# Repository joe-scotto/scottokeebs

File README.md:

ScottoKeebs at its core is an extensive collection of freely available handwired keyboard and macropad projects. It was started in September of 2022 and since then over 19 projects have been released. Most of them fit on a common 220x220mm 3D printer, require minimal support material, and use either an Arduino Pro Micro or a more powerful Raspberry Pi Pico.

# Navigation

-   [Website](https://scottokeebs.com)
-   [Keyboards](https://scottokeebs.com/blogs/keyboards)
-   [Macropads](https://scottokeebs.com/blogs/macropads)
-   [Extras](https://github.com/joe-scotto/scottokeebs/tree/main/Extras)
-   [Discord](https://discord.gg/vN6X3z8eyv)
-   [YouTube](https://youtube.com/joe_scotto)
-   [Recommendations](https://scottokeebs.com/pages/recommendations)
-   [Handwiring](https://www.youtube.com/watch?v=hjml-K-pV4E)
-   [Shop](https://www.youtube.com/watch?v=hjml-K-pV4E)

# Supporting

The ScottoKeebs project is released entirely for free and always will be, however, the development of new boards is completely out of my own pocket. It’s not a particularly expensive project to maintain but does involve quite a bit of time between prototyping and making content related to them.

**If you happen to really enjoy what I do and want to support me, consider [donating](https://donate.stripe.com/eVa14Yev83SmavmbII), [becoming a patron](https://patreon.com/joe_scotto), or purchasing something from my [shop](https://www.scottokeebs.com/shop).**

# License

</a></p>

<p xmlns:cc="http://creativecommons.org/ns#" xmlns:dct="http://purl.org/dc/terms/"><a property="dct:title" rel="cc:attributionURL" href="https://github.com/joe-scotto/scottokeebs">ScottoKeebs</a> by <a rel="cc:attributionURL dct:creator" property="cc:attributionName" href="https://github.com/joe-scotto">Joe Scotto</a> is licensed under <a href="http://creativecommons.org/licenses/by-nc-sa/4.0/?ref=chooser-v1" target="_blank" rel="license noopener noreferrer" style="display:inline-block;">CC BY-NC-SA 4.0

_If you plan on converting a ScottoKeeb to a PCB, I would prefer you don't release the production or design files publicly in order to prevent people from stealing and selling my designs._

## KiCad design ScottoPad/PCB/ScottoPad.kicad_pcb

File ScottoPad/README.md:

# ScottoPad (SK33)

The ScottoPad is an 18-key wireless macropad.

You can read more about the components and how to build it [here](https://scottokeebs.com/blogs/macropads/scottopad-handwired-macropad).

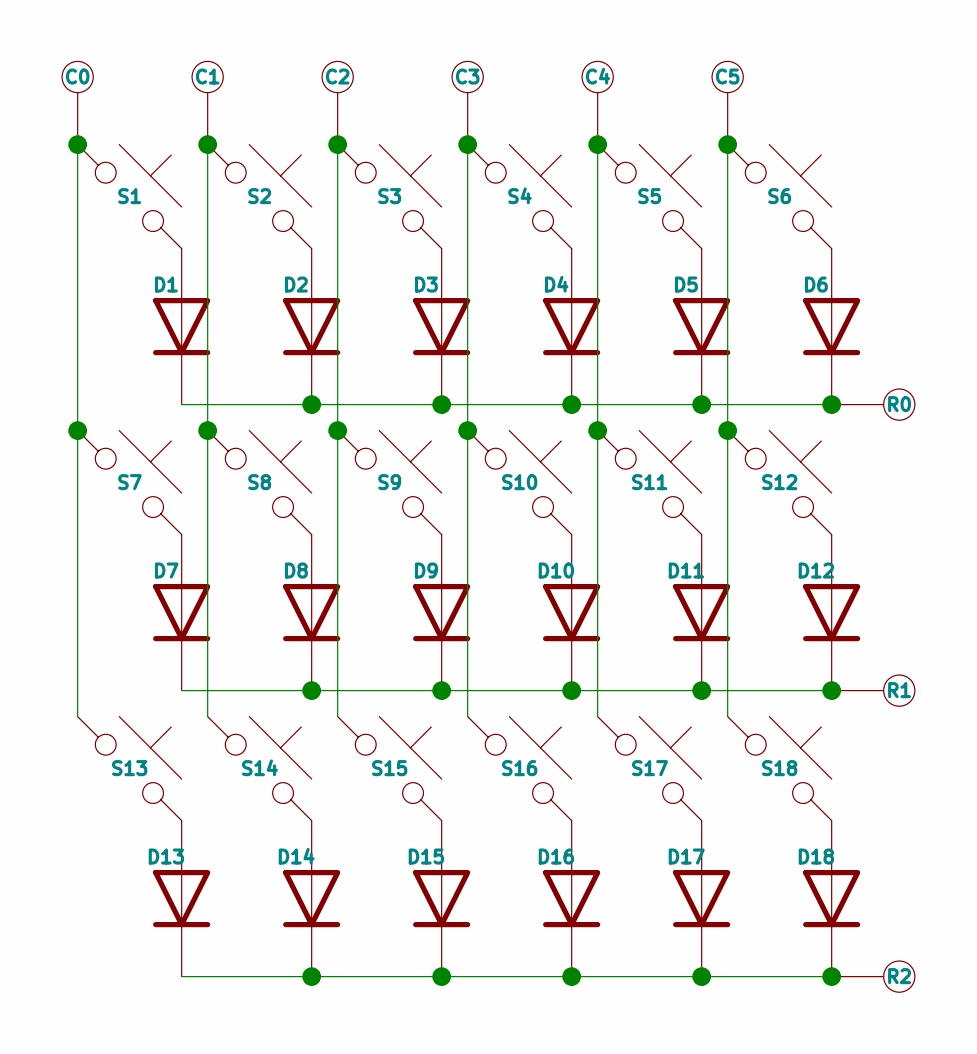
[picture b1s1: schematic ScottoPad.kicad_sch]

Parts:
C0, C1, C2, C3, C4, C5: TestPoint
D1, D2, D3, D4, D5, D6, D7, D8, D9, D10, D11, D12, D13, D14, D15, D16, D17, D18: Diode; Diode_SOD-123
R0, R1, R2: TestPoint
S1, S2, S3, S4, S5, S6, S7, S8, S9, S10, S11, S12, S13, S14, S15, S16, S17, S18: Keyswitch; MX_Solder_1.00u

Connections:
unnamed: C0.1, S1.1, S7.1, S13.1
unnamed: C1.1, S2.1, S8.1, S14.1
unnamed: C2.1, S3.1, S9.1, S15.1
unnamed: C3.1, S4.1, S10.1, S16.1
unnamed: C4.1, S5.1, S11.1, S17.1
unnamed: C5.1, S6.1, S12.1, S18.1
unnamed: D1.2 (A), S1.2
unnamed: D1.1 (K), D2.1 (K), D3.1 (K), D4.1 (K), D5.1 (K), D6.1 (K), R0.1
unnamed: D2.2 (A), S2.2
unnamed: D3.2 (A), S3.2
unnamed: D4.2 (A), S4.2
unnamed: D5.2 (A), S5.2
unnamed: D6.2 (A), S6.2
unnamed: D7.2 (A), S7.2
unnamed: D8.2 (A), S8.2
unnamed: D9.2 (A), S9.2
unnamed: D10.2 (A), S10.2
unnamed: D7.1 (K), D8.1 (K), D9.1 (K), D10.1 (K), D11.1 (K), D12.1 (K), R1.1
unnamed: D11.2 (A), S11.2
unnamed: D12.2 (A), S12.2
unnamed: D13.2 (A), S13.2
unnamed: D13.1 (K), D14.1 (K), D15.1 (K), D16.1 (K), D17.1 (K), D18.1 (K), R2.1
unnamed: D14.2 (A), S14.2
unnamed: D15.2 (A), S15.2
unnamed: D16.2 (A), S16.2
unnamed: D17.2 (A), S17.2
unnamed: D18.2 (A), S18.2

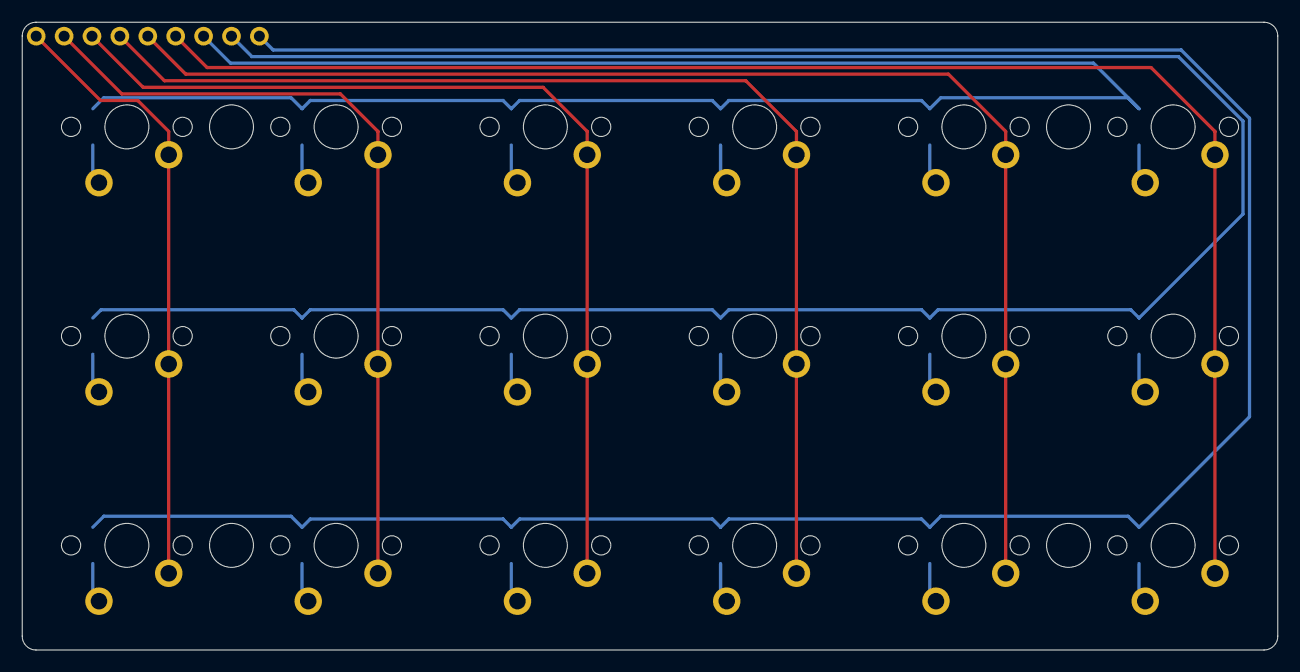
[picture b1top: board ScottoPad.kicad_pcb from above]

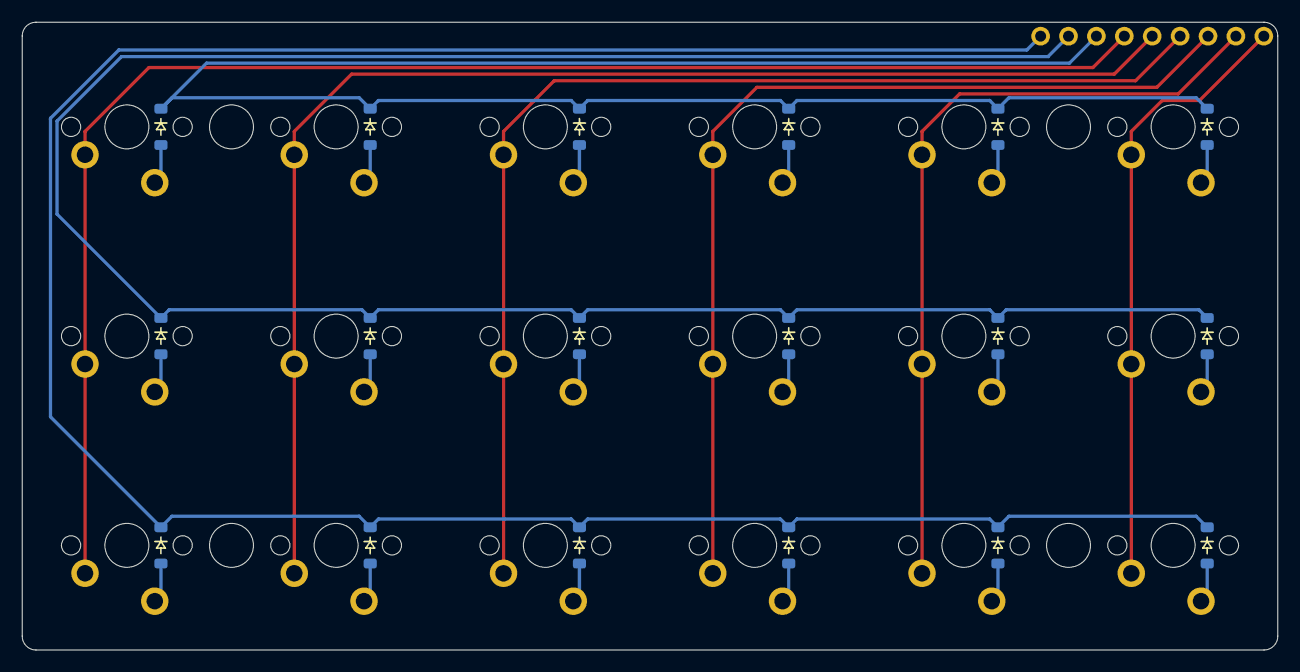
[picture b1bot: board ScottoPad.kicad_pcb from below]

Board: 2 copper layers, 114.3 x 57.2 mm, 45 parts (18 on the bottom side), 27 nets.

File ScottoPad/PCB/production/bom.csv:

Designator,Footprint,Quantity,Value,LCSC Part #
"C0, C1, C2, C3, C4, C5, R0, R1, R2",TestPoint,9,TestPoint,
"D1, D10, D11, D12, D13, D14, D15, D16, D17, D18, D2, D3, D4, D5, D6, D7, D8, D9",Diode_SOD-123,18,Diode,
"S1, S10, S11, S12, S13, S14, S15, S16, S17, S18, S2, S3, S4, S5, S6, S7, S8, S9",MX_Solder_1.00u,18,Keyswitch,

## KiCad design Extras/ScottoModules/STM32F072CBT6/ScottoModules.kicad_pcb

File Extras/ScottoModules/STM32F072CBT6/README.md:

# ScottoModules

Two modules based on the STM32F072CBT6 to make integrated MCU PCBs simpler. They're designed to sit between 2 switches on an ortholinear or row-staggered keyboard, column-staggered will require some manual moving to get them to fit correctly.

# Bill of Materials (BOM)

| Quantity | Part                        | LCSC                                                                               |
| -------- | --------------------------- | ---------------------------------------------------------------------------------- |
| 1        | STM32F072CBT6 (LQFP-48_7x7) | [C81720](https://jlcpcb.com/partdetail/Stmicroelectronics-STM32F072CBT6/C81720)    |
| 1        | XC6206 (SOT-23-3L)          | [C5446](https://jlcpcb.com/partdetail/TorexSemicon-XC6206P332MRG/C5446)            |
| 1        | USBLC6-2SC6 (SOT-23-6)      | [C2827654](https://jlcpcb.com/partdetail/TechPublic-USBLC62SC6/C2827654)           |
| 1        | TL3342                      | [C115351](https://jlcpcb.com/partdetail/Alpsalpine-SKQGABE010/C115351)             |
| 1        | USB_C_HRO_TYPE-C-31-M-12    | [C165948](https://jlcpcb.com/partdetail/Korean_HropartsElec-TYPE_C_31_M12/C165948) |
| 2        | 5.1k Resistor (0402)        | [C25905](https://jlcpcb.com/partdetail/26648-0402WGF5101TCE/C25905)                |
| 1        | 10k Resistor (0402)         | [C25744](https://jlcpcb.com/partdetail/26487-0402WGF1002TCE/C25744)                |
| 1        | 500mA Fuse (0603)           | [C210357](https://jlcpcb.com/partdetail/Bourns-MF_FSMF050X2/C210357)               |
| 3        | 1uF Capacitor (0402)        | [C52923](https://jlcpcb.com/partdetail/53938-CL05A105KA5NQNC/C52923)               |
| 1        | 10nF Capacitor (0402)       | [C15195](https://jlcpcb.com/partdetail/15869-CL05B103KB5NNNC/C15195)               |
| 2        | 4.7uF Capacitor (0402)      | [C23733](https://jlcpcb.com/partdetail/24469-CL05A475MP5NRNC/C23733)               |
| 5        | 100nF Capacitor (0402)      | [C307331](https://jlcpcb.com/partdetail/291005-CL05B104KB54PNC/C307331)            |

# Usage

1. The project is setup as a Kicad template, first open Kicad and select "New Project from Template..." from the file menu.

2. Next click the folder icon and navigate to where you saved the `ScottoModules/STM32F072CBT6` folder and open it.

3. Select `ScottoModules (STM32)` and click `OK`.

4. Name your project and save it somewhere.

5. You're now ready to start using ScottoModules!

# Kicad Template Folder

Alternatively, you can save `ScottoModules/STM32F072CBT6` to your Kicad templates folder and not have to manually load it each time.

-   **Mac** - /Users/YOUR_USERNAME/Documents/KiCad/8.0/template/
-   **Windows** - C:\Users\YOUR_USERNAME\Documents\KiCad\8.0\template\

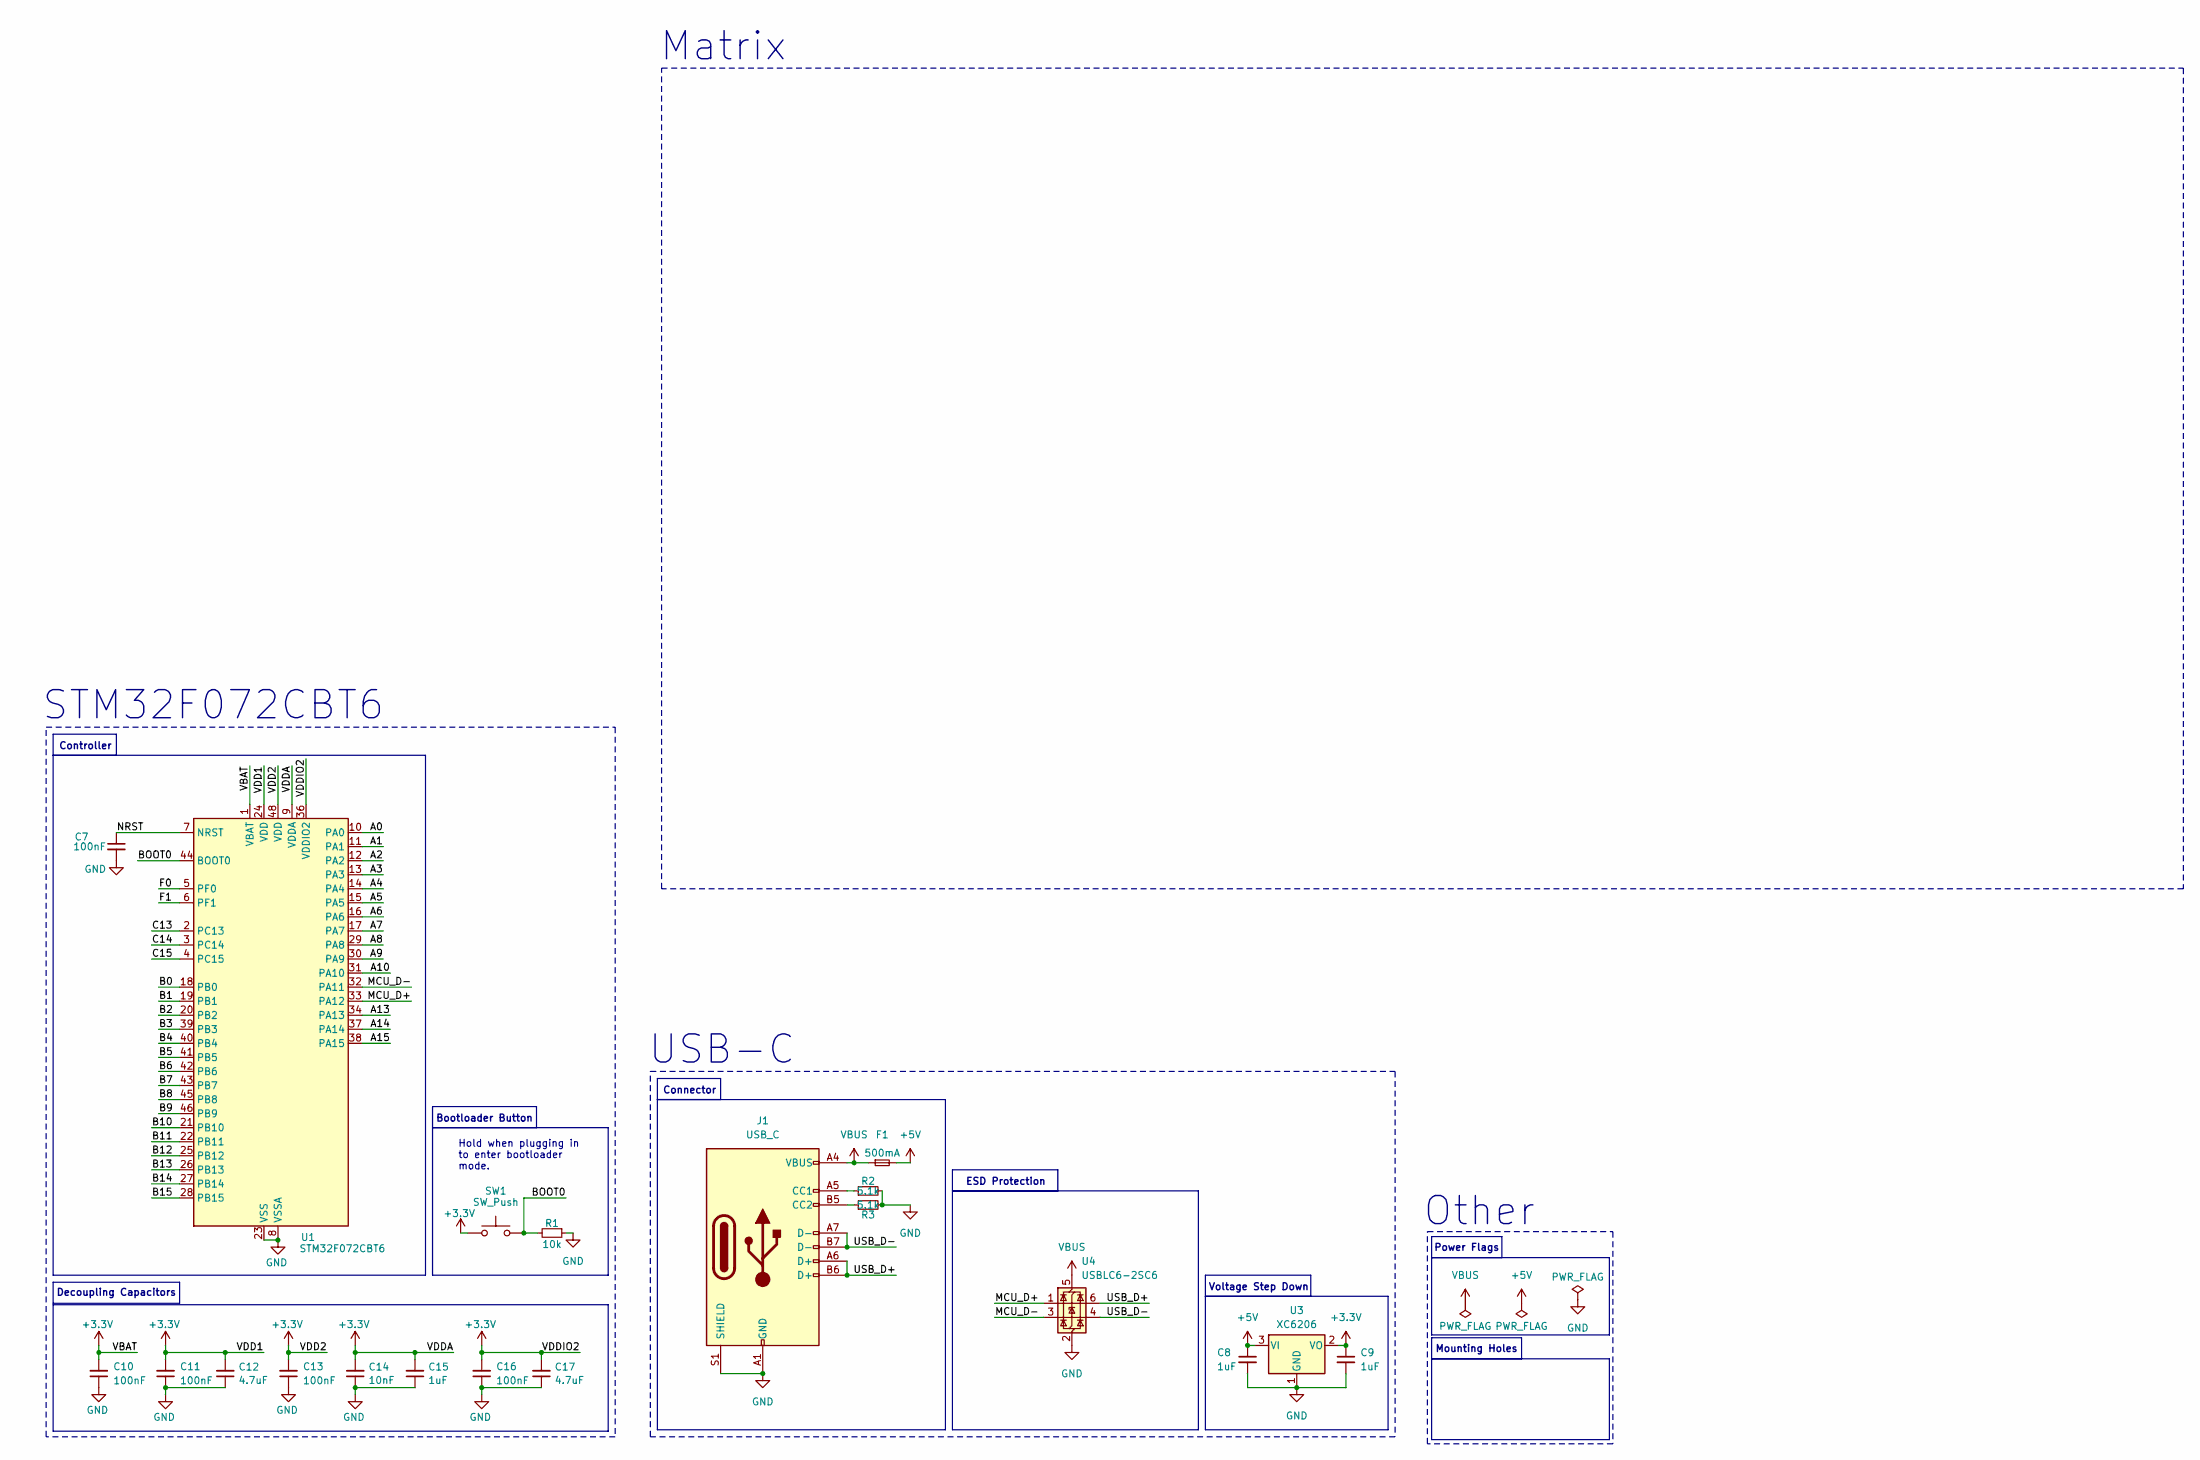
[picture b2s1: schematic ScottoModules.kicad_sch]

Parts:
C7: 100nF; Capacitor_0402; LCSC C307331
C8, C9: 1uF; Capacitor_0402; LCSC C52923
C10, C11, C13, C16: 100nF; Capacitor_0402; MPN CL05B104KB54PNC; LCSC C307331
C12, C17: 4.7uF; Capacitor_0402; MPN CL05A475MP5NRNC; LCSC C23733
C14: 10nF; Capacitor_0402; MPN CL05B103KB5NNNC; LCSC C15195
C15: 1uF; Capacitor_0402; MPN CL05A105KA5NQNC; LCSC C52923
F1: 500mA; Fuse_0603; LCSC C210357
J1: USB_C; USB_C_HRO_TYPE-C-31-M-12; LCSC C165948
R1: 10k; Resistor_0402; LCSC C25744
R2, R3: 5.1k; Resistor_0402; LCSC C25905
SW1: SW_Push; Button_TL3342; LCSC C115351
U1: STM32F072CBT6; Package_LQFP-48_7x7mm_P0.5; LCSC C81720
U3: XC6206; Voltage_SOT-23; LCSC C5446
U4: USBLC6-2SC6; ESD_SOT-23-6; LCSC C2827654

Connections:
+3.3V: C9.1, C10.2, C11.2, C12.2, C13.2, C14.2, C15.2, C16.2, C17.2, SW1.1, U1.1 (VBAT), U1.9 (VDDA), U1.24 (VDD), U1.36 (VDDIO2), U1.48 (VDD), U3.2 (VO)
+5V: C8.1, F1.2, U3.3 (VI)
/A0: U1.10 (PA0)
/A1: U1.11 (PA1)
/A2: U1.12 (PA2)
/A3: U1.13 (PA3)
/A4: U1.14 (PA4)
/A5: U1.15 (PA5)
/A6: U1.16 (PA6)
/A7: U1.17 (PA7)
/A8: U1.29 (PA8)
/A9: U1.30 (PA9)
/A10: U1.31 (PA10)
/A13: U1.34 (PA13)
/A14: U1.37 (PA14)
/A15: U1.38 (PA15)
/B0: U1.18 (PB0)
/B1: U1.19 (PB1)
/B2: U1.20 (PB2)
/B3: U1.39 (PB3)
/B4: U1.40 (PB4)
/B5: U1.41 (PB5)
/B6: U1.42 (PB6)
/B7: U1.43 (PB7)
/B8: U1.45 (PB8)
/B9: U1.46 (PB9)
/B10: U1.21 (PB10)
/B11: U1.22 (PB11)
/B12: U1.25 (PB12)
/B13: U1.26 (PB13)
/B14: U1.27 (PB14)
/B15: U1.28 (PB15)
/BOOT0: R1.2, SW1.2, U1.44 (BOOT0)
/C13: U1.2 (PC13)
/C14: U1.3 (PC14)
/C15: U1.4 (PC15)
/F0: U1.5 (PF0)
/F1: U1.6 (PF1)
/MCU_D+: U1.33 (PA12), U4.1 (I/O1)
/MCU_D-: U1.32 (PA11), U4.3 (I/O2)
/NRST: C7.1, U1.7 (NRST)
/USB_D+: J1.A6 (D+), J1.B6 (D+), U4.6 (I/O1)
/USB_D-: J1.A7 (D-), J1.B7 (D-), U4.4 (I/O2)
GND: C7.2, C8.2, C9.2, C10.1, C11.1, C12.1, C13.1, C14.1, C15.1, C16.1, C17.1, J1.A1 (GND), J1.A12 (GND), J1.B1 (GND), J1.B12 (GND), J1.S1 (SHIELD), R1.1, R2.2, R3.2, U1.8 (VSSA), U1.23 (VSS), U1.35 (VSS), U1.47 (VSS), U3.1 (GND), U4.2 (GND)
unnamed: J1.A5 (CC1), R2.1
unnamed: J1.B5 (CC2), R3.1
VBUS: F1.1, J1.A4 (VBUS), J1.A9 (VBUS), J1.B4 (VBUS), J1.B9 (VBUS), U4.5 (VBUS)

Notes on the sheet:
Hold when plugging in to enter bootloader mode.
STM32F072CBT6
USB-C
Mounting Holes
Decoupling Capacitors
Controller
ESD Protection
Power Flags
Voltage Step Down
Other
Bootloader Button
Matrix
Connector

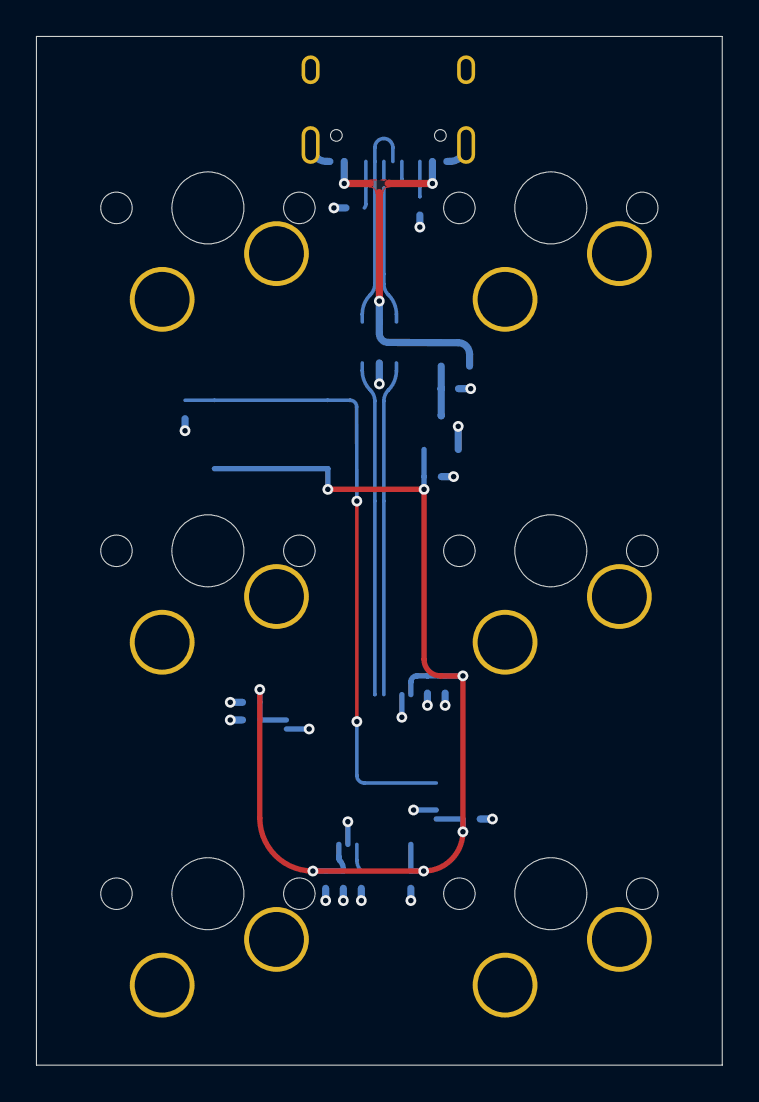
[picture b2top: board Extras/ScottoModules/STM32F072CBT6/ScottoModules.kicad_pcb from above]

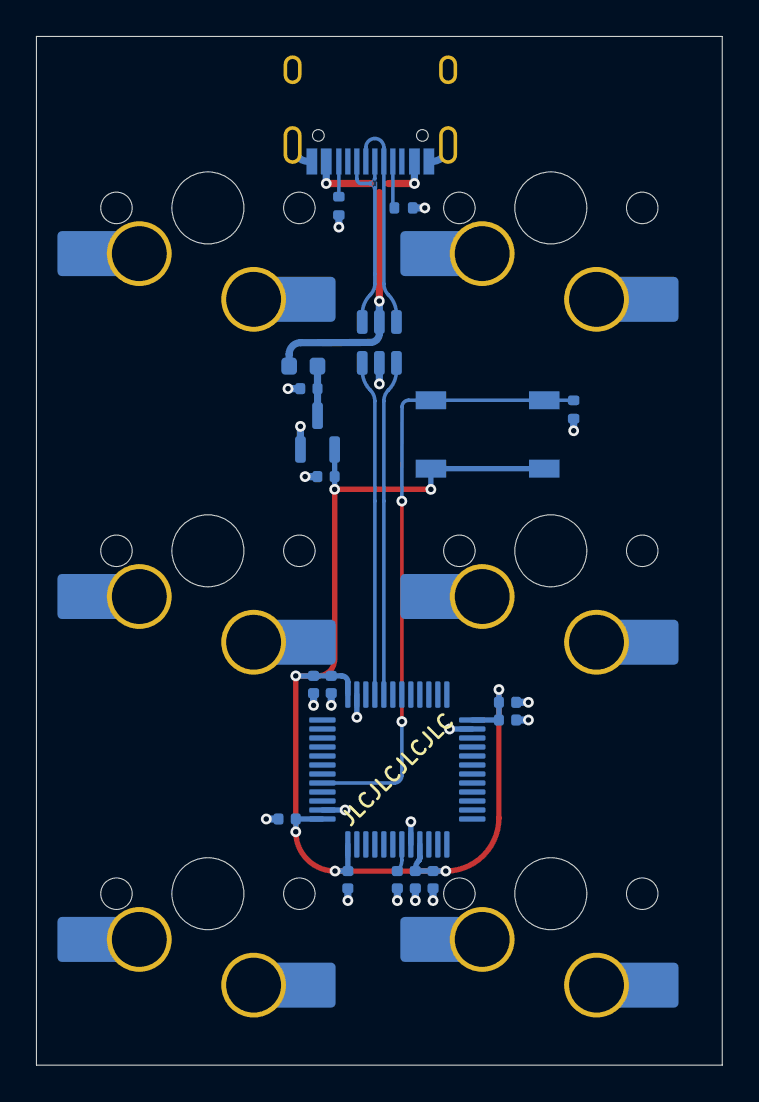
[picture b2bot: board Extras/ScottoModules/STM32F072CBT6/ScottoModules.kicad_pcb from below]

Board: 4 copper layers, 38.1 x 57.2 mm, 20 parts (20 on the bottom side), 12 nets.

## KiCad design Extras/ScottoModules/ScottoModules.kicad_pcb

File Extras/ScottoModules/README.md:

# ScottoModules

Two modules based on the STM32F072CBT6 to make integrated MCU PCBs simpler. They're designed to sit between 2 switches on an ortholinear or row-staggered keyboard, column-staggered will require some manual moving to get them to fit correctly.

# Bill of Materials (BOM)

| Quantity | Part                        | LCSC                                                                               |
| -------- | --------------------------- | ---------------------------------------------------------------------------------- |
| 1        | STM32F072CBT6 (LQFP-48_7x7) | [C81720](https://jlcpcb.com/partdetail/Stmicroelectronics-STM32F072CBT6/C81720)    |
| 1        | XC6206 (SOT-23-3L)          | [C5446](https://jlcpcb.com/partdetail/TorexSemicon-XC6206P332MRG/C5446)            |
| 1        | USBLC6-2SC6 (SOT-23-6)      | [C2827654](https://jlcpcb.com/partdetail/TechPublic-USBLC62SC6/C2827654)           |
| 1        | TL3342                      | [C115351](https://jlcpcb.com/partdetail/Alpsalpine-SKQGABE010/C115351)             |
| 1        | USB_C_HRO_TYPE-C-31-M-12    | [C165948](https://jlcpcb.com/partdetail/Korean_HropartsElec-TYPE_C_31_M12/C165948) |
| 2        | 5.1k Resistor (0402)        | [C25905](https://jlcpcb.com/partdetail/26648-0402WGF5101TCE/C25905)                |
| 1        | 10k Resistor (0402)         | [C25744](https://jlcpcb.com/partdetail/26487-0402WGF1002TCE/C25744)                |
| 1        | 500mA Fuse (0603)           | [C210357](https://jlcpcb.com/partdetail/Bourns-MF_FSMF050X2/C210357)               |
| 2        | 1uF Capacitor (0402)        | [C52923](https://jlcpcb.com/partdetail/53938-CL05A105KA5NQNC/C52923)               |
| 1        | 10uF Capacitor (0603)       | [C19702](https://jlcpcb.com/partdetail/20411-CL10A106KP8NNNC/C19702)               |
| 6        | 100nF Capacitor (0402)      | [C307331](https://jlcpcb.com/partdetail/291005-CL05B104KB54PNC/C307331)            |

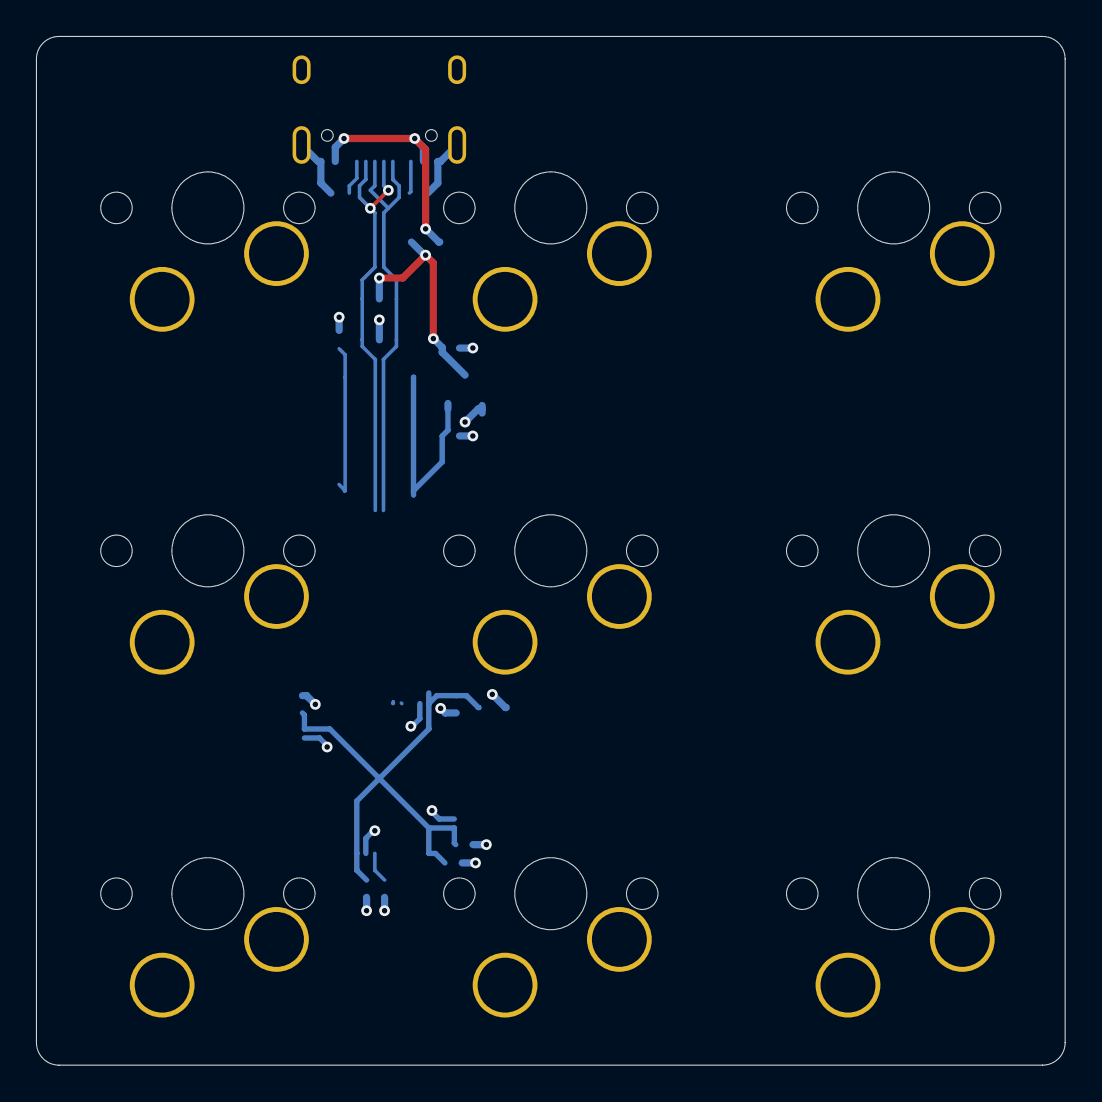
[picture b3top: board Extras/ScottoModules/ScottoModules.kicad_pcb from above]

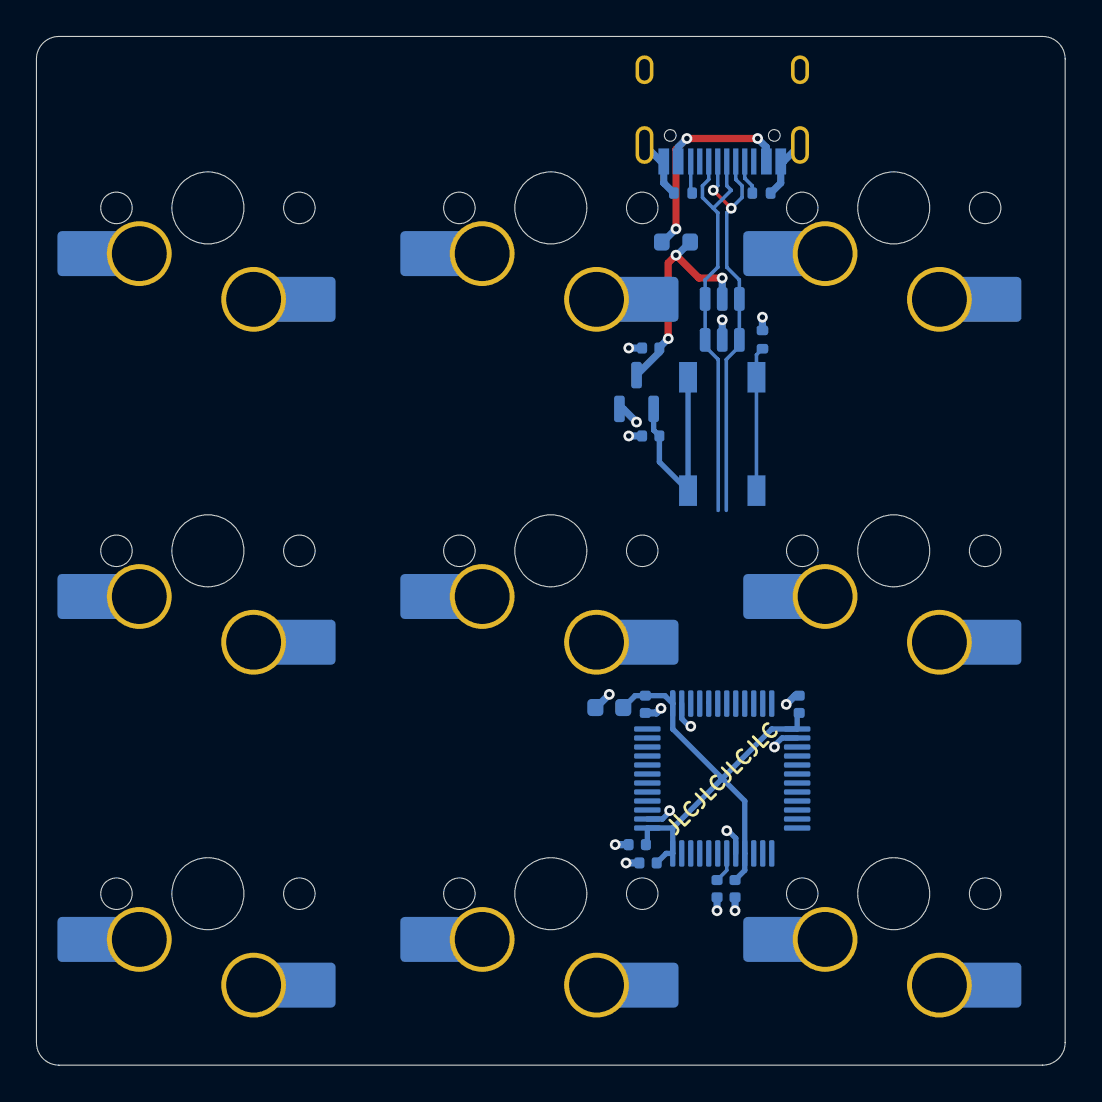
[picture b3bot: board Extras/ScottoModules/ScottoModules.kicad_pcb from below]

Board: 2 copper layers, 57.2 x 57.1 mm, 27 parts (27 on the bottom side), 15 nets.

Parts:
C1, C2, C3, C4, C5, C7: 100nF; Capacitor_0402
C6: 10uF; Capacitor_0603
C8, C9: 1uF; Capacitor_0402
F1: 500mA; Fuse_0603
J1: USB_C; USB_C_HRO_TYPE-C-31-M-12
R1: 10k; Resistor_0402
R2, R3: 5.1k; Resistor_0402
S1, S2, S3, S4, S4#2, S4#3, S5, S6, S6#2: Keyswitch; MX_1.00u
SW1: SW_Push; Button_TL3342
U1: STM32F072CBT6; Package_LQFP-48_7x7mm_P0.5
U3: XC6206; Voltage_SOT-23
U4: USBLC6-2SC6; ESD_SOT-23-6

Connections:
+3.3V: C1.2, C2.2, C3.2, C4.2, C5.2, C6.2, C9.1, SW1.1, U1.1 (VBAT), U1.9 (VDDA), U1.24 (VDD), U1.36 (VDDIO2), U1.48 (VDD), U3.2 (VO)
+5V: C8.1, F1.2, U3.3 (VI), U4.5 (VBUS)
BOOT0: R1.2, SW1.2, U1.44 (BOOT0)
D+: J1.A6 (D+), J1.B6 (D+), U1.33 (PA12), U4.1 (I/O1), U4.6 (I/O1)
D-: J1.A7 (D-), J1.B7 (D-), U1.32 (PA11), U4.3 (I/O2), U4.4 (I/O2)
GND: C1.1, C2.1, C3.1, C4.1, C5.1, C6.1, C7.2, C8.2, C9.2, J1.A1 (GND), J1.A12 (GND), J1.B1 (GND), J1.B12 (GND), J1.S1 (SHIELD), R1.1, R2.2, R3.2, U1.8 (VSSA), U1.23 (VSS), U1.35 (VSS), U1.47 (VSS), U3.1 (GND), U4.2 (GND)
unnamed: S4.2, S4#2.2, S4#3.2
unnamed: S6.2, S6#2.2
unnamed: J1.A5 (CC1), R2.1
unnamed: J1.B5 (CC2), R3.1
unnamed: S1.1, S4.1, S4#2.1, S4#3.1
unnamed: S2.1, S5.1
unnamed: S3.1, S6.1, S6#2.1
unnamed: C7.1, U1.7 (NRST)
VBUS: F1.1, J1.A4 (VBUS), J1.A9 (VBUS), J1.B4 (VBUS), J1.B9 (VBUS)

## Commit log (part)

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2024-05-31 Fix missing pads
2024-05-31 Allow bridged mask
2024-06-03 Scotto37 Prototype
2024-06-03 Add numbers to keyboards
2024-06-04 Add ScottoSlant PCB
2024-06-04 Add new files
2024-06-04 Add USB cutout to thin wall case
2024-06-09 Add left-handed firmware thanks to @Crosslasher
2024-06-11 Add ScottoWing (PCB Edition) QWERTY ZMK source
2024-06-16 Working Scotto37
2024-06-16 Add Vial
2024-06-16 Remove vial RGB
2024-06-16 Fix vial
2024-06-16 Add vial config
2024-06-25 Add Choc HS 1.00u, MX Solder 1.00u reversable, testpoint, and 2765 joystick
2024-06-26 Update Joystick
2024-06-28 Fix missing 3x6 case
2024-06-30 Add Template
2024-06-30 Update placement to be cleaner
2024-07-01 Update gitignore
2024-07-09 ScottoHazard
2024-07-09 Rename files
2024-07-09 ScottoHazard mostly ready to build
2024-07-13 Rename reset to boot button for clarity
2024-07-13 Double labels not needed for differential pair
2024-07-13 Fix README typo.
    A note on the phrase here. Technically and legally speaking, you can't prevent someone form sharing the source they make as a derivative work of any item in the project that is under the license. Tha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
2024-07-13 Added MPN
2024-07-13 Added Power Flags
2024-07-13 Modified PCB Project
2024-07-13 Update to better V2
2024-07-13 Should be final
2024-07-13 Update readme files
2024-07-14 Ignore .DS_Store
2024-07-15 Update schematic
2024-07-15 Cleanup tracks and vias
2024-07-15 Convert T-Junctions to filled zones
2024-07-15 Regroup
2024-07-16 Add resistor and led
2024-07-16 Add 0805
2024-07-17 Update choc to use proper positioning for JLC
2024-07-18 Add ScottoLong (PCB Edition) Case
2024-07-18 Update Choc 3D position
2024-07-18 Add port
2024-07-22 Add layout file
2024-07-22 Update firmware to use layout file
2024-07-23 Update firmware to proper layout method
2024-07-23 Add license header
2024-07-23 Add macro
2024-07-23 Update keymap
2024-07-27 Remove V1
2024-07-27 Remove zip files
2024-08-25 Update testpoint dimensinos and add 16x16 choc
2024-08-29 Add EC11
2024-08-29 Add EC11 3D model
2024-09-01 Add combo mx ec11
2024-09-01 Add plate
2024-09-01 Update plate
2024-09-02 Firmware
2024-09-05 Firmware compiling
2024-09-05 Final firmware for now until I build the thing in which then I'll probably find out something isn't right but for now it's probably right
2024-09-07 Keycaps
2024-09-08 Add Seeed RP2040 XIAO
2024-09-14 Add Scotto69 (PCB Edition) case
2024-09-14 Update case files
2024-09-14 Update KLE to include encoder for Vial
2024-09-14 KLE Update
2024-09-14 Add firmware
2024-09-14 Add new flat caps and update shapr3d file
2024-09-17 Update QMK
2024-09-17 Fix duplicated 1,1 matrix
2024-09-19 Add RP2040 Stamp
2024-09-19 Add stamp as symbol footprint
2024-09-19 Final case files for Scotto69 (PCB Edition)
2024-09-20 Update SK6812MINI and 4 Port Hub
2024-09-23 Update led footprint
2024-10-14 Update gaming layer
2024-10-24 Add KB2040
2024-10-24 Add 2 port 35
2024-10-26 Add horizontal arrows
2024-10-27 Add Case
2024-10-27 Add README.md
2024-10-29 Add ZMK Studio support
2024-10-29 Update firmware to include QWERTY
2024-11-01 Fix missing indents
2024-11-01 Update magnet offset
2024-11-21 Add choc homing
2024-11-22 Add ScottoCyberdeck
2024-11-22 Move ScottoCyberdeck to Extras
2024-11-23 Update bezel
2024-11-25 Add K3-1204D switch
2024-12-15 Add single directory download link.
2024-12-17 Update cyberdeck?
2024-12-18 Update components
2024-12-19 Component changes
2024-12-22 Add firmware files
2024-12-22 Remove case files
2024-12-22 Add case files
2024-12-29 Update VIAL UID
2024-12-30 Finalize Scotto44
2024-12-30 R7;2uChange under to dash
2025-01-07 Update vial
2025-01-15 Update QWERTY
2025-01-19 Update Scotto40
2025-01-19 Update MX Hotswap footprint
2025-01-24 Add SMD KB2040
2025-01-27 Add QTPY 2040
2025-02-12 Updated Pico
2025-02-12 Update ScottoKicad
2025-02-17 Add Sculpted keycaps
2025-02-17 Add all rows
2025-03-04 Add K3-1204D-L
2025-03-07 Add 3D model for new switch
2025-03-08 Update to correct files
2025-03-14 Add JST PH
2025-03-31 update diode markers
2025-04-05 Add ScottoPad
2025-04-05 Add readme
2025-04-06 Update solder switch
2025-04-06 Add test for layer 2
2025-04-07 Fix ZMK studio
2025-04-22 CNC Version
2025-04-22 Add Carvera footprints
2025-04-24 Add 16x16mm
2025-04-25 Add 16x16 function key
2025-05-08 Add Scotto16 macropad
2025-06-09 Add Scotto34 V2 case for Keycon
2025-06-10 Add CNC files
2025-06-26 Update some Kicad stuff
2025-06-30 Add hotkeys
2025-07-02 Add start of ScottoKatana PCB
2025-07-02 Add more config
2025-07-02 Add triple tap for right command key in iTerm2
2025-07-12 Add RGUI tap dance for iTerm 2 compatibility
2025-07-13 Start Scotto20
2025-07-13 Update firmware to use solenoid buzz
2025-07-13 Update to use RP2040 pro micro
2025-07-15 Update 3D files
2025-07-15 Final case files
2025-07-15 Add NextPCB sponsor tag
2025-07-17 Add CAM file for MCU Cover
2025-08-01 Add .clang-format file
2025-08-01 Update clang
2025-08-03 Update MCU cover
2025-08-03 Add clangd
2025-08-03 Ignore compile commands from nvim setup
2025-08-06 Add positioning points
2025-08-06 RP2040 Zero changes
2025-08-06 Add PCB
2025-08-07 ScottoHousing for USB-C connectors
2025-08-09 Add working scottohousing
2025-08-10 Add USB-A housings
2025-08-17 Semi-working right
2025-08-17 Add shift lock
2025-08-17 Extract combos to own files
2025-08-17 Add layer names and remove headers
2025-08-18 Rename layer
2025-08-18 Update mapping
2025-08-21 ALT/CTRL lock
2025-09-05 Add X mods and combos for slowly moving to 24 key layout :O
2025-09-07 Start relying less on thumbs
2025-09-09 Strip to just mac layout in prep for os_toggle
2025-09-09 Strip copyright section for now
2025-09-09 Add code combo also
2025-09-09 Formatting
2025-09-09 Working-ish layers
2025-09-10 Update clang-format
2025-09-10 Move to keys.h and keys.c
2025-09-12 Remove tap only unregisters
2025-09-12 Mapping mostly done i think
2025-09-12 Finished changes to personal map
2025-09-12 Move gaming layer down so other layers work
2025-09-13 Keymap finished for now I guess
2025-09-13 No need for a windows layer anymore
2025-09-13 No need for a dedicated gaming layer anymore either.
2025-09-13 Remove imports
2025-09-13 Add a mode check text
2025-09-15 No need to reset on every plug-in
2025-09-15 Fix mode typer and eeprom reads
2025-09-15 QWERTY swap working
2025-09-15 Flip from is_mac to is_windows
2025-09-15 Fix imports
2025-09-16 Update to new mapping fully
2025-09-16 Final changes, probably, but honestly probably not, fuck, shit, piss
2025-09-16 Remove debug shit that doesn't work I think umm
2025-10-06 Symbol layer green mods
2025-10-06 Working right side mapping without hold layer done
2025-10-06 Add F10
2025-10-06 Add left handed version
2025-10-06 Update firmware
2025-10-23 Add case files and keycaps for Bambu
2025-10-23 Finish up firmware
2025-10-24 Fix formatting and update image in README.md
2025-10-25 Update keycap stem and plate
2025-10-29 Fix missing color
2025-10-29 Add tab to symbol layer also
2025-10-29 Update left
2025-10-29 Update right
2025-10-29 Update num lock
2025-10-29 Remove duplicate number equal combo
2025-10-29 Add tab to number layer
2025-10-29 Add reset feature
2025-10-29 Add reset to right layout
2025-10-30 Update naming
2025-10-30 Make cleaner combos for reset and os toggle
2025-10-30 Clean up
2025-10-30 Final keymaps
2025-11-07 Add 2x2 spacebar
2025-11-09 Start ScottoKia
2025-11-10 Add start of mapping
2025-11-10 working map
2025-11-10 Add keycaps
2025-11-11 Add ScottoT9
2025-11-12 Update image in README.md for ScottoT9
2025-11-18 Replace ESC with TAB
2025-11-21 Update diodes and add solder choc
2025-11-22 Update OLED
2025-11-23 Add 1.5 and 1.75 choc solder
2025-11-23 Add sponsorship section for NextPCB
    Added sponsorship acknowledgment for NextPCB.
2025-11-25 Create SECURITY.md for security policy
    Add a security policy document outlining supported versions and reporting procedures.
2025-11-26 Add my personal OLED footprint
2025-11-26 Start PCB Edition
2025-11-27 Fix geometry
2025-12-08 Update files
2025-12-09 Change image link in README.md
    Updated image reference for ScottoT9 PCB Edition.
2025-12-10 Add OLED animations
2025-12-10 Add .uf2
2025-12-11 Rename info.json to keyboard.json
2025-12-23 Add 16x16 solder
2025-12-25 Add ScottoShrink
2025-12-25 Update to newer corner radius
2025-12-25 Update to more modern Scotto mapping
2025-12-25 Update to modern keymap
2025-12-25 Update special layer to rgui for windows
2025-12-25 Gaming mode should be a normal layer
2025-12-25 Use RCTL on game mode
2025-12-29 Update README with sponsorship and image change
    Added sponsorship information and updated image link.
2026-01-05 Add files via upload
    OpenSCAD 2D key switch plate. Enables export to cnc compatible formats like svg, dxf, etc.
2026-01-05 Rename Plate.scad file for consistency
2026-01-05 Remove unused scale and text modules
    Removed unused modules for vertical and horizontal scales, title, and calibration text to clean up the code.
2026-01-07 Update app key
2026-01-09 Update 128x64 OLED to proper dimensions
2026-01-11 Add ScottoRang
2026-01-11 Move to handwired folder
2026-01-15 Add ScottoScripts
2026-01-15 Update frames folder
2026-01-15 Remove frames.txt from tracking
2026-01-15 Update scripts
2026-01-15 Read and write fps for oled.c
2026-01-15 Actually use OLED_TIMOUT
2026-01-15 Include frames.c after
2026-01-15 Use matrix oled animation
2026-01-19 Default to monow
2026-01-22 Add GPIO to rp2040 and update oled
2026-02-09 Add MTF standoff
2026-02-11 Add PCB Edition firmware
2026-02-12 Update port cutout on case
2026-02-14 Add sponsor tag
2026-03-06 Add design files
2026-03-06 Start keymap
2026-03-06 Update KLE
2026-03-06 Firmware prepped
2026-03-07 Update to new folder structure
2026-03-07 Update folder structure
2026-03-07 Working firmware
2026-04-09 Add Raw keycap bases for custom legends
2026-04-20 Update Scotto108
2026-04-25 Update to RP2040
2026-04-28 Add plate mount stabilizer option
2026-04-28 Remove identifiers
2026-05-07 Add Scotto2
2026-05-15 Actually add files lol
2026-06-05 Add RP2040 Flipped MX reverse mount
2026-06-11 Start firmware
2026-06-17 Add YD2040 Pico
2026-06-23 Ready for release, mostly
2026-06-24 Add keymap file
2026-06-24 Convert Vial to be the QWERTY map
2026-06-26 Update mouse layer to have zxcvb and a for copy past etc
2026-06-26 Add ESC to mouse layer

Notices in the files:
README.md:
https://mirrors.creativecommons.org/presskit/icons/cc.svg?ref=chooser-v1https://mirrors.creativecommons.org/presskit/icons/by.svg?ref=chooser-v1https://mirrors.creativecommons.org/presskit/icons/nc.svg?ref=chooser-v1
